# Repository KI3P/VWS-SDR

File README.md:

# Vienna Wireless Society Software Defined Receiver (VWS-SDR)

This repository contains the files for a 2025 project by the [Vienna Wireless Society's](https://viennawireless.net/wp/) Makers Group. This project aims to build the RF front end of a software defined receiver covering the HF bands. The goals of the project are: 

1. Learn how to use KiCAD, and 
2. Learn surface mount assembly techniques. 

## Credit

The VWS-SDR design draws heavily from the RF board of the T41-EP Software Defined Transceiver (SDT) originally designed by Al Peter-AC8GY and Jack Purdum-W8TEE. The T41-EP is a self-contain SDT that does not require an external PC, laptop, or tablet to use. Al and Jack wrote a book, available on [Amazon](https://www.amazon.com/dp/B0D25FV48C), describing the theory and operation of the T41-EP.

Thanks to Rick W1DSP for writing the Quisk integration, Barry KV4FV for the gnuradio demodulation flowgraph, the many T41 contributors for the hardware and software derived from that project, and to Leon NT8B, Dean KK4DAS, Mark KM4GML, Vlad K4LRZ, and Ed KQ4RVX for their help designing, building, and testing the prototypes.

## Design overview 

The VWS-SDR has stages shown in the block diagram below.

1. A gain stage based on the [GALI-S66+](https://www.minicircuits.com/WebStore/dashboard.html?model=GALI-S66%2B) MMIC amplifier.
2. A [Tayloe Mixer](http://norcalqrp.org/files/Tayloe_mixer_x3a.pdf) that uses quadrature signals generated by a [Si5351](https://www.digikey.com/en/htmldatasheets/production/1316951/0/0/1/si535x-tmstk) clock generator and a [74CBTLV3253](https://www.ti.com/product/SN74CBTLV3253) 2-channel analog multiplexer to mix the RF signals to IF.
3. An anti-aliasing low-pass filter followed by a USB soundcard to digitize the IF signal.
4. Demodulation is performed in software using [quisk](http://james.ahlstrom.name/quisk/) or [gnuradio](https://www.gnuradio.org/).

To modify the PCB design, download this repository to your computer. Open the `KiCad\VWS-SDR-ref-design.kicad_pro` file using the [KiCad](https://www.kicad.org/) EDA software package. This repository includes a few custom symbols and footprints that should automatically be added to your library lists by KiCad.

## Code

### Pico

You two equivalent choices for the code that will run on the Pico. If you prefer C code written in the Arduino framework, use that. If you prefer micropython code, load that code instead. 

#### Arduino framework

The `code/pico_sketch` folder contains an Arduino sketch to program the Pico. The sketch listens for ASCII commands on the USB serial bus (baud 115200) that match this format:

`FR 123456`

where `123456` is the frequency in Hertz that the Si5351 should be tuned to.

Open the sketch in the Arduino IDE and configure Arduino to have the settings shown below under the Tools menu. For “Port” select whatever COM port appears when you plug the Pico into your computer with a USB cable.

Then compile and load the sketch onto the pico by clicking the Upload button (Sketch->Upload).

The Pico sketch configures the Si5351 to produce 10 MHz tones on start. You can confirm this by connected an oscilloscope to the CLK0 and CLK1 outputs where you should see something like the screen shot below.

You can manually change the frequency using the Serial Monitor window in the Arduino. The Pico communicates at a baud rate of 115200 and expects commands in the form: “FR 123456” where 123456 is the frequency in Hz.

For instance, to tune the center of the band to 7070 kHz, enter the following command:

You should get the reply “OK” and an invitation to enter a new frequency. The CLK0 and CLK1 outputs should now show an output at 7070 kHz.

#### Micropython framework

The `code/pico_micropython` folder contains micropython code for the Pico written by Rick W1DSP. It works similarly to the Arduino sketch, the only difference is commands are terminated by a newline (`\n`) in the Python code, versus carriage return (`\r`) in the sketch. If the preferred tuner is the sketch, just edit this line in `code/VWS-Quisk/vwsquiskpkg/quisk_hardware.py`:

```python
   self.serial.write(b'FR %d\r'%(vfo+correction))
```

And change to `\r` to `\n`.  The original thinking in using Python for the VWS was to facilitate the extensive driver libraries Adafruit provides for their peripherals, as well as the ease of use and velocity of development Python brings to low speed control applications.

To install the Python tuner, the Pico must first be loaded with CircuitPython as described [here](https://learn.adafruit.com/getting-started-with-raspberry-pi-pico-circuitpython/circuitpython). Once CircuitPython is installed and booted, you will see a virtual disk drive for the board appear.  On my machine it is `/media/rick/CIRCUITPY`.

To run the tuner, copy `code/pico_micropython/{code.py,vws_tuner.py}`
to the virtual disk drive, and power cycle the board.  To verify operation, connnect to the serial port associated with the board (here, it is `/dev/ttyACM0`, 115200 bps), and type a carriage return.  You should see a `tune>` prompt, and entering a command like `FR 7074000` will cause the 5351 to tune to 7.074 Mhz. As required by the VWS SDR designs, clk0/clk1 are in quadrature. The Python script works similarly to various 5351 libraries to generate quadrature clocks: PLLA is a integer multiple of the desired frequency (factor of 4).

### Computer

Demodulation of the audio can be done in gnuradio or Quisk.

#### Gnuradio

Credit to Barry KV4FV for his contributions to the gnuradio code.

The `code/gnuradio_KI3P` contains a [gnuradio](https://wiki.gnuradio.org/index.php/InstallingGR) flowgraph to display the received signal and perform audio demodulation. It also allows you to adjust the gain and phase balance between the L and R channels to improve sideband separation if needed.

#### Quisk

Credit to Rick W1DSP for the Quisk code and instructions. Quisk links:

* [Quisk documentation](https://james.ahlstrom.name/quisk/docs.html)
* [Quisk github](https://github.com/jimahlstrom/quisk)
* [Install Quisk](https://james.ahlstrom.name/quisk/docs.html#Installation)

##### Install VWS-Quisk package

Once quisk is installed, copy the `code/VWS-Quisk/vwsquiskpkg` directory into the quisk distribution directory. On my computer this is:

* `/usr/lib/python3/dist-packages/quisk`

Note: This is the way new radios are introduced to the quisk radio configuration manager: for a new radio named `xyzzy`, you create a directory named `xyzzypkg` in the quisk directory, and write a `quisk_hardware.py` module.  Python class inheritance will define most of the necessary routines, but functionally you'll want open/close/tune method as shown in the `vwsquiskpkg` version.

##### Configure Quisk

Launch quisk.

To add the VWS SDR as a radio, click the Config Button, then select the Radios tab. In the Radios config panel, select the "Add a new radio with the general type", and select the VWS SDR item, name the radio "VWS"

You should see a new Radio appear just below the title bar named "VWS".  Click that item, and then select the Hardware tab.  Enter the serial port name (in my case it was `/dev/ttyACM0`). Click the Sound tab, and choose appropriate settings for "Radio Sound Output" and "Microphone Input" that correspond to your soundcard.  In Digital Rx0 line, select `pulse: Use name QuiskDigitalOutput.monitor`.  Of course, you'll need to have loaded the pulse audio system.  Note that I have not tested any of this on Mac or Windows, and wouldn't expect it to work out of the box on either system type.

Back on the Config->Radios screen, select VWS in the "When Quisk starts, use the radio" line. In the Config tab, quisk provides the ability to adjust IQ balance via "Adjust receive amplitude and phase".  I manually adjusted this using a signal generator tuned to the vicinity of 14.074 mhz, and then saved the result.

##### Configure WSJT-X if desired

To use the WSJT-X integration, use the package manager to install wsjtx, or build from source. 

I've been starting wsjtx manually within quisk: Click Config, select the Config tab, then look for the Start WSJT-X item.  The drop down menu has an option Main Rx0 Now item - select that and quisk will start the wsjtx application.  Once you've fully debugged the quisk:wsjtx integration,
setting "Start WSJT-X" to "Main Rx0 on startup" on the Config menus, Config tab will automatically start up wstjx when quisk starts.

The included screen captures show some of the details of getting quisk to interoperate with wsjtx.  Note that quisk won't stream audio on `QuiskDigitalOutput.monitor` unless you're in a digital mode (see DGT-U).

Quisk can be controlled by hamlib.  In the Config screens, select the VWS radio, then Remote tab.  On the Remote config screen, set the port to 4532.  You'll have to restart quisk for the setting to take effect.  After this is done, you can use `rigctl -m 2` to test: for example, the command `F 14074000` will tune quisk to the FT8 band on 20M.  Once the hamlib integration has been confirmed as working, you'll be able to control quisk via the wsjtx application, i.e. switching bands, frequencies in that app, and quisk following along as a normal radio would.

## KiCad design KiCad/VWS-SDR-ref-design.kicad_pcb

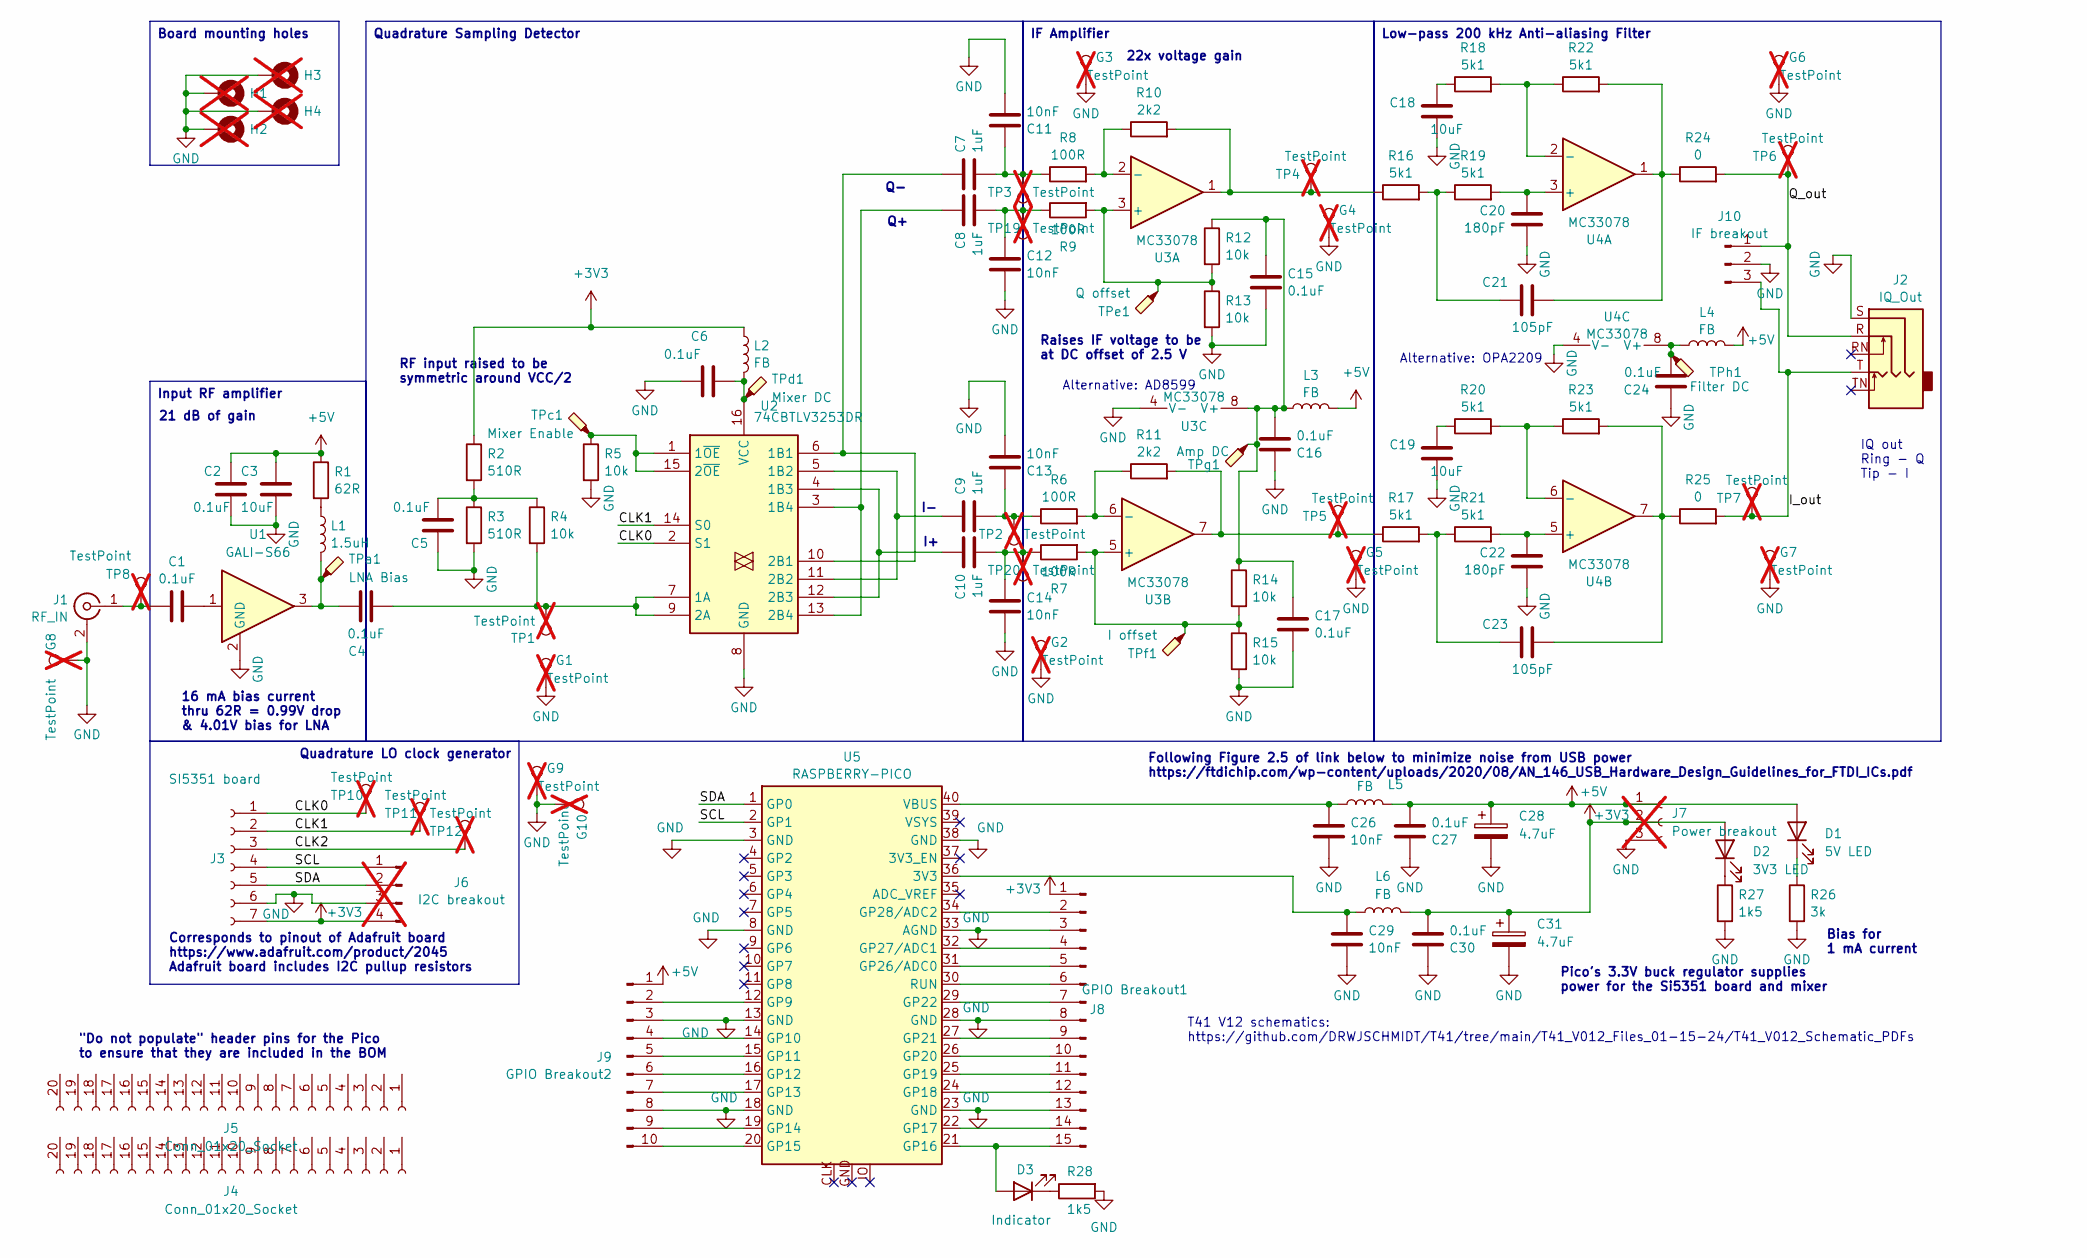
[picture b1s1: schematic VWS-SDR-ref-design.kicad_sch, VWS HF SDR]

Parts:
C1, C2, C4, C5, C6, C15, C16, C17, C24, C27, C30: 0.1uF; C_1206_3216Metric_Pad1.33x1.80mm_HandSolder; Mouser Part Number C1206C104K5RACTU
C3, C18, C19: 10uF; C_1206_3216Metric_Pad1.33x1.80mm_HandSolder; Mouser Part Number 80-C1206C106K4P
C7, C8, C9, C10: 1uF; C_1206_3216Metric_Pad1.33x1.80mm_HandSolder; Mouser Part Number 187-CL31B105KBHNNNE
C11, C12, C13, C14, C26, C29: 10nF; C_1206_3216Metric_Pad1.33x1.80mm_HandSolder; Mouser Part Number 80-C1206C103K5R7210
C20, C22: 180pF; C_1206_3216Metric_Pad1.33x1.80mm_HandSolder; Mouser Part Number 791-1206B181K160CT
C21, C23: 105pF; C_1206_3216Metric_Pad1.33x1.80mm_HandSolder; Mouser Part Number 581-12065C101KAT2A
C28, C31: 4.7uF; CP_Radial_D5.0mm_P2.00mm; Mouser Part Number 80-ESK475M016AC3AA
D1: 5V LED; LED_1206_3216Metric_Pad1.42x1.75mm_HandSolder; MPN APTD3216LCGCK
D2: 3V3 LED; LED_1206_3216Metric_Pad1.42x1.75mm_HandSolder; MPN APTD3216LSYCK
D3: Indicator; LED_1206_3216Metric_Pad1.42x1.75mm_HandSolder; MPN APTD3216LSYCK
G1, G2, G3, G4, G5, G6, G7, G8, G9, G10: TestPoint; PinHeader_1x01_P2.54mm_Vertical; not fitted
H1, H2, H3, H4: MountingHole_4.3mm_M4_DIN965_Pad; not fitted
J1: RF_IN; SMA_Vertical_and_Edgemount; Mouser Part Number 712-CONSMA001-G
J2: IQ_Out; Jack_3.5mm_STX-3081_Horizontal; Mouser Part Number 490-SJ1-3515N
J3: SI5351 board; Adafruit_Si5351
J4, J5: Conn_01x20_Socket
J6: I2C breakout; PinHeader_1x04_P2.54mm_Vertical; not fitted
J7: Power breakout; PinHeader_1x03_P2.54mm_Vertical; not fitted
J8: GPIO Breakout1; PinSocket_1x15_P2.54mm_Vertical
J9: GPIO Breakout2; PinSocket_1x10_P2.54mm_Vertical
J10: IF breakout; PinSocket_1x03_P2.54mm_Vertical
L1: 1.5uH; R_1206_3216Metric_Pad1.30x1.75mm_HandSolder; Mouser Part Number 81-LQM31PN1R5M00L
L2, L3, L4, L5, L6: FB; R_1206_3216Metric_Pad1.30x1.75mm_HandSolder; Mouser Part Number 875-HZ1206E601R-10
R1: 62R; R_1206_3216Metric_Pad1.30x1.75mm_HandSolder; Mouser Part Number 652-CR1206FX-62R0ELF
R2, R3: 510R; R_1206_3216Metric_Pad1.30x1.75mm_HandSolder; Mouser Part Number 652-CR1206FX-5100ELF
R4, R5, R12, R13, R14, R15: 10k; R_1206_3216Metric_Pad1.30x1.75mm_HandSolder; Mouser Part Number 652-CR1206FX-1002ELF
R6, R7, R8, R9: 100R; R_1206_3216Metric_Pad1.30x1.75mm_HandSolder; Mouser Part Number 652-CR1206FX-1000ELF
R10, R11: 2k2; R_1206_3216Metric_Pad1.30x1.75mm_HandSolder; Mouser Part Number 652-CR1206FX-2201ELF
R16, R17, R18, R19, R20, R21, R22, R23: 5k1; R_1206_3216Metric_Pad1.30x1.75mm_HandSolder; Mouser Part Number 652-CR1206JW-512ELF
R24, R25: 0; R_1206_3216Metric_Pad1.30x1.75mm_HandSolder; Mouser Part Number 71-CRCW12060000Z0EAC
R26: 3k; R_1206_3216Metric_Pad1.30x1.75mm_HandSolder; MPN CR1206-FX-3001ELF
R27, R28: 1k5; R_1206_3216Metric_Pad1.30x1.75mm_HandSolder; MPN CR1206-FX-1501ELF
TP1, TP2, TP3, TP4, TP5, TP6, TP7, TP8, TP10, TP11, TP12, TP19, TP20: TestPoint; PinHeader_1x01_P2.54mm_Vertical; not fitted
TPa1: LNA Bias; TestPoint_Pad_D1.5mm
TPc1: Mixer Enable; TestPoint_Pad_D1.5mm
TPd1: Mixer DC; TestPoint_Pad_D1.5mm
TPe1: Q offset; TestPoint_Pad_D1.5mm
TPf1: I offset; TestPoint_Pad_D1.5mm
TPg1: Amp DC; TestPoint_Pad_D1.5mm
TPh1: Filter DC; TestPoint_Pad_D1.5mm
U1: GALI-S66; SOT-89-3; Mouser Part Number 139-GALI-S66
U2: 74CBTLV3253DR; SOIC-16_3.9x9.9mm_P1.27mm; Mouser Part Number 595-SN74CBTLV3253DR
U3, U4: MC33078; SOIC-8_3.9x4.9mm_P1.27mm; Mouser Part Number 595-MC33078DR
U5: RASPBERRY-PICO; Raspberry_pico_pin_or_castellation_footprint; Mouser Part Number 358-SC0915

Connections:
+3V3: C30.1, C31.1, D2.2 (A), J3.7, J6.4, J7.2, J8.1, L2.1, L6.2, R2.1
+5V: C2.2, C3.2, C27.1, C28.1, D1.2 (A), J7.1, J9.1, L3.2, L4.2, L5.2, R1.1
/CLK0: J3.1, TP10.1, U2.2 (S1)
/CLK1: J3.2, TP11.1, U2.14 (S0)
/CLK2: J3.3, TP12.1
/I_out: J2.T, J10.3, R25.2, TP7.1
/Q_out: J2.R, J10.1, R24.2, TP6.1
/SCL: J3.4, J6.1, U5.2 (GP1)
/SDA: J3.5, J6.2, U5.1 (GP0)
GND: C2.1, C3.1, C5.1, C6.1, C11.1, C12.1, C13.1, C14.1, C15.1, C16.2, C17.1, C18.1, C19.1, C20.1, C22.1, C24.2, C26.1, C27.2, C28.2, C29.1, C30.2, C31.2, G1.1, G2.1, G3.1, G4.1, G5.1, G6.1, G7.1, G8.1, G9.1, G10.1, H1.1, H2.1, H3.1, H4.1, J1.2 (Ext), J2.S, J3.6, J6.3, J7.3, J8.3, J8.8, J8.13, J9.3, J9.8, J10.2, R3.2, R5.2, R13.2, R15.2, R26.2, R27.2, R28.2, U1.2 (GND), U2.8 (GND), U3.4 (V-), U4.4 (V-), U5.3 (GND), U5.8 (GND), U5.13 (GND), U5.18 (GND), U5.23 (GND), U5.28 (GND), U5.33 (AGND), U5.38 (GND)
unnamed: C1.2, U1.1
unnamed 11: C4.1, L1.2, TPa1.1, U1.3; also elsewhere on the board
unnamed: C5.2, R2.2, R3.1, R4.1
unnamed: C10.1, C14.2, R7.1, TP20.1
unnamed: C7.1, C11.2, R8.1, TP3.1
unnamed: C8.1, C12.2, R9.1, TP19.1
unnamed: C9.1, C13.2, R6.1, TP2.1
unnamed: C18.2, R18.1
unnamed: C19.2, R20.1
unnamed: C21.1, R22.2, R24.1, U4.1
unnamed: C21.2, R16.2, R19.1
unnamed: C23.1, R23.2, R25.1, U4.7
unnamed: C23.2, R17.2, R21.1
unnamed: D1.1 (K), R26.1
unnamed: D2.1 (K), R27.1
unnamed: D3.2 (A), J8.15, U5.21 (GP16)
unnamed: D3.1 (K), R28.1
unnamed: C1.1, J1.1 (In), TP8.1
unnamed: J8.2, U5.34 (GP28/ADC2)
unnamed: J8.4, U5.32 (GP27/ADC1)
unnamed: J8.5, U5.31 (GP26/ADC0)
unnamed: J8.6, U5.30 (RUN)
unnamed: J8.7, U5.29 (GP22)
unnamed: J8.9, U5.27 (GP21)
unnamed: J8.10, U5.26 (GP20)
unnamed: J8.11, U5.25 (GP19)
unnamed: J8.12, U5.24 (GP18)
unnamed: J8.14, U5.22 (GP17)
unnamed: J9.2, U5.12 (GP9)
unnamed: J9.4, U5.14 (GP10)
unnamed: J9.5, U5.15 (GP11)
unnamed: J9.6, U5.16 (GP12)
unnamed: J9.7, U5.17 (GP13)
unnamed: J9.9, U5.19 (GP14)
unnamed: J9.10, U5.20 (GP15)
unnamed: L1.1, R1.2
unnamed: R10.2, R16.1, TP4.1, U3.1
unnamed: R11.2, R17.1, TP5.1, U3.7
unnamed 48: C4.2, R4.2, TP1.1, U2.7 (1A), U2.9 (2A); also elsewhere on the board
unnamed: C7.2, U2.6 (1B1), U2.10 (2B1)
unnamed: C9.2, U2.5 (1B2), U2.11 (2B2)
unnamed: C10.2, U2.4 (1B3), U2.12 (2B3)
unnamed: C8.2, U2.3 (1B4), U2.13 (2B4)
unnamed 53: R5.1, TPc1.1, U2.1 (1~OE), U2.15 (2~OE); also elsewhere on the board
unnamed 54: C6.2, L2.2, TPd1.1, U2.16 (VCC); also elsewhere on the board
unnamed 55: R9.2, R12.2, R13.1, TPe1.1, U3.3 (+); also elsewhere on the board
unnamed: R8.2, R10.1, U3.2 (-)
unnamed 57: R7.2, R14.2, R15.1, TPf1.1, U3.5 (+); also elsewhere on the board
unnamed: R6.2, R11.1, U3.6 (-)
unnamed 59: C15.2, C16.1, C17.2, L3.1, R12.1, R14.1, TPg1.1, U3.8 (V+); also elsewhere on the board
unnamed: C20.2, R19.2, U4.3 (+)
unnamed: R18.2, R22.1, U4.2 (-)
unnamed: C22.2, R21.2, U4.5 (+)
unnamed: R20.2, R23.1, U4.6 (-)
unnamed 64: C24.1, L4.1, TPh1.1, U4.8 (V+); also elsewhere on the board
unnamed: C29.2, L6.1, U5.36 (3V3)
unnamed: C26.2, L5.1, U5.40 (VBUS)

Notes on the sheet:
Raises IF voltage to be at DC offset of 2.5 V
T41 V12 schematics: https://github.com/DRWJSCHMIDT/T41/tree/main/T41_V012_Files_01-15-24/T41_V012_Schematic_PDFs
Bias for 1 mA current
Following Figure 2.5 of link below to minimize noise from USB power https://ftdichip.com/wp-content/uploads/2020/08/AN_146_USB_Hardware_Design_Guidelines_for_FTDI_ICs.pdf
Pico's 3.3V buck regulator supplies power for the Si5351 board and mixer
Alternative: OPA2209
21 dB of gain
Alternative: AD8599
"Do not populate" header pins for the Pico to ensure that they are included in the BOM
16 mA bias current thru 62R = 0.99V drop & 4.01V bias for LNA
IQ out Ring - Q Tip - I
22x voltage gain
RF input raised to be symmetric around VCC/2
Corresponds to pinout of Adafruit board https://www.adafruit.com/product/2045 Adafruit board includes I2C pullup resistors
Quadrature LO clock generator
IF Amplifier
Low-pass 200 kHz Anti-aliasing Filter
Quadrature Sampling Detector
Input RF amplifier
Board mounting holes

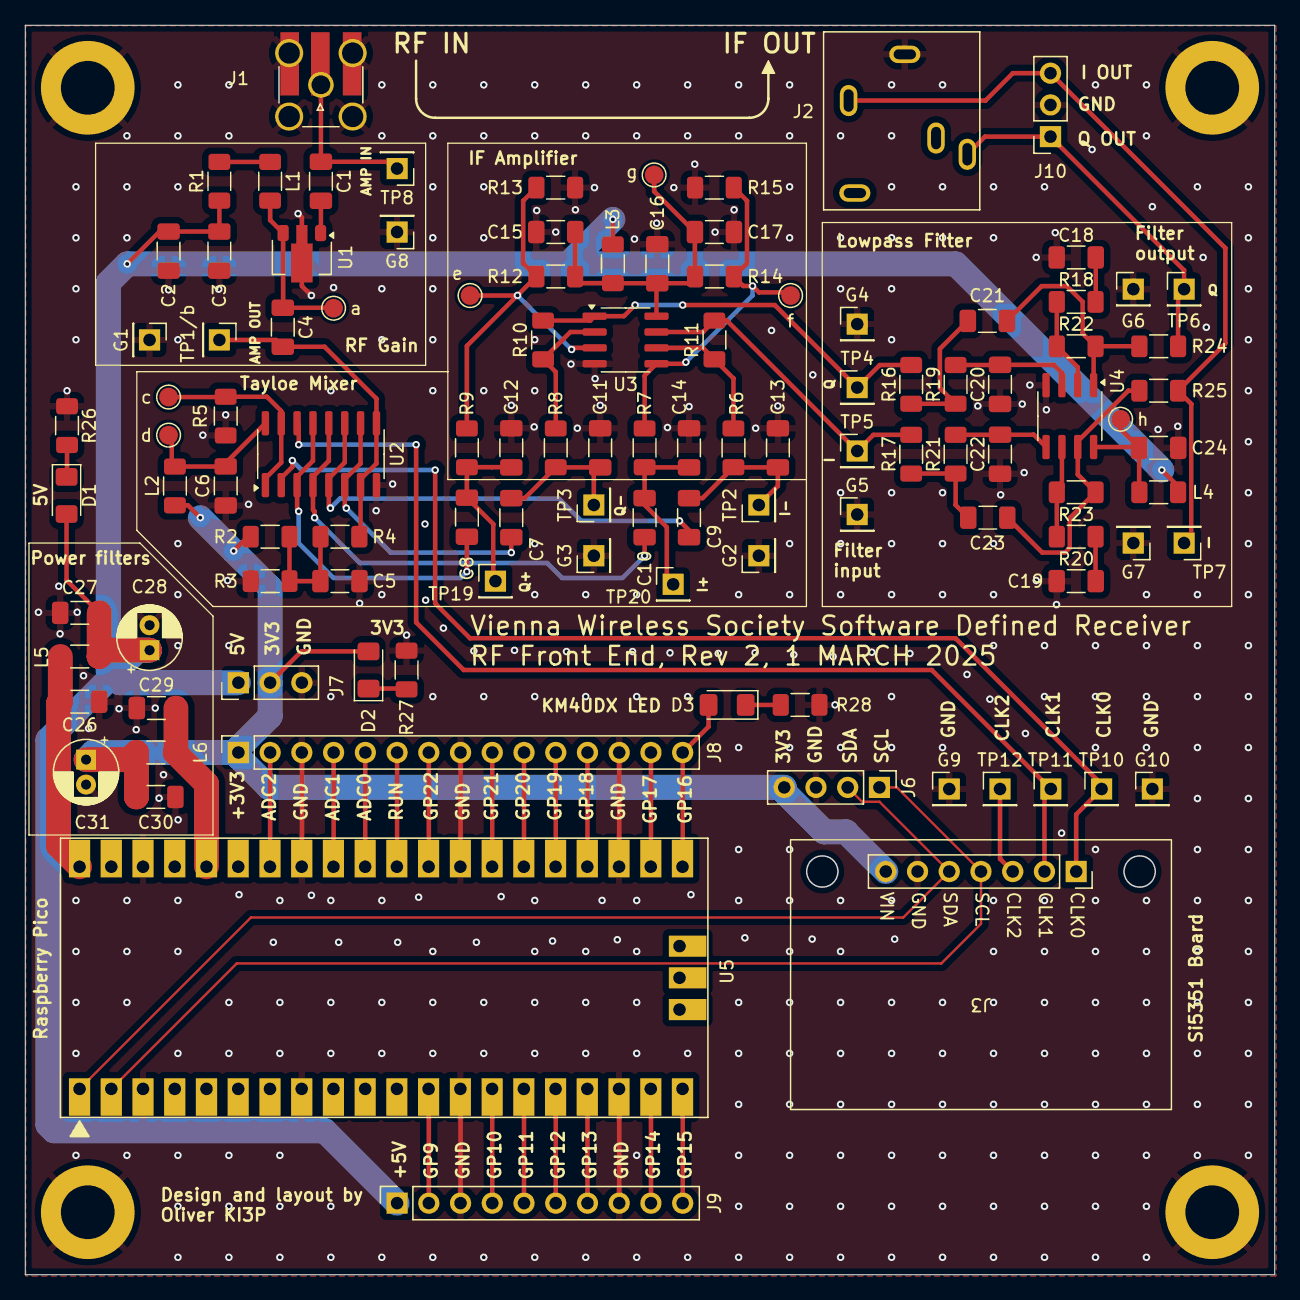
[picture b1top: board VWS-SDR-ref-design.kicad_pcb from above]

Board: 4 copper layers, 99.9 x 99.9 mm, 114 parts (0 on the bottom side), 67 nets.

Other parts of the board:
TP1/b: TestPoint; PinHeader_1x01_P2.54mm_Vertical
a: LNA Bias; TestPoint_Pad_D1.5mm
c: Mixer Enable; TestPoint_Pad_D1.5mm
d: Mixer DC; TestPoint_Pad_D1.5mm
e: Q offset; TestPoint_Pad_D1.5mm
f: I offset; TestPoint_Pad_D1.5mm
g: Amp DC; TestPoint_Pad_D1.5mm
h: Filter DC; TestPoint_Pad_D1.5mm

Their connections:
unnamed 11: a.1; also elsewhere on the board
unnamed 48: TP1/b.1; also elsewhere on the board
unnamed 53: c.1; also elsewhere on the board
unnamed 54: d.1; also elsewhere on the board
unnamed 55: e.1; also elsewhere on the board
unnamed 57: f.1; also elsewhere on the board
unnamed 59: g.1; also elsewhere on the board
unnamed 64: h.1; also elsewhere on the board

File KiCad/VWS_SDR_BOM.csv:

"Reference","Value","Footprint","Qty","DNP","Tayda","Adafruit PN","MPN"
"C1,C2,C4,C5,C6,C15,C16,C17,C24,C27,C30","0.1uF","Capacitor_SMD:C_1206_3216Metric_Pad1.33x1.80mm_HandSolder","11","","","","C1206C104K5RACTU"
"C3,C18,C19","10uF","Capacitor_SMD:C_1206_3216Metric_Pad1.33x1.80mm_HandSolder","3","","","","C1206C106K4PACTU"
"C7,C8,C9,C10","1uF","Capacitor_SMD:C_1206_3216Metric_Pad1.33x1.80mm_HandSolder","4","","","","KGM31HR71C105KU"
"C11,C12,C13,C14,C26,C29","10nF","Capacitor_SMD:C_1206_3216Metric_Pad1.33x1.80mm_HandSolder","6","","","","C1206C103K5RAC7210"
"C20,C22","180pF","Capacitor_SMD:C_1206_3216Metric_Pad1.33x1.80mm_HandSolder","2","","","","KGM31BCG2A181FT"
"C21,C23","105pF","Capacitor_SMD:C_1206_3216Metric_Pad1.33x1.80mm_HandSolder","2","","","","C3216C0G2J101G060AA"
"C28,C31","4.7uF","Capacitor_THT:CP_Radial_D5.0mm_P2.00mm","2","","","","ESK475M016AC3AA"
"D1","5V LED","LED_SMD:LED_1206_3216Metric_Pad1.42x1.75mm_HandSolder","1","","","","APTD3216LCGCK"
"D2","3V3 LED","LED_SMD:LED_1206_3216Metric_Pad1.42x1.75mm_HandSolder","1","","","","APTD3216LSYCK"
"D3","Indicator","LED_SMD:LED_1206_3216Metric_Pad1.42x1.75mm_HandSolder","1","","","","APTD3216LSYCK"
"G1,G2,G3,G4,G5,G6,G7,G8,G9,G10,TP1,TP2,TP3,TP4,TP5,TP6,TP7,TP8,TP10,TP11,TP12,TP19,TP20","TestPoint","Connector_PinHeader_2.54mm:PinHeader_1x01_P2.54mm_Vertical","23","DNP","","",""
"J1","RF_IN","VWS-SDR:SMA_Vertical_and_Edgemount","1","","","","CONSMA001-G"
"J2","IQ_Out","VWS-SDR:Jack_3.5mm_STX-3081_Horizontal","1","","","","SJ1-3515N"
"J3","SI5351 board","VWS-SDR:Adafruit_Si5351","1","","","2045",""
"J4,J5","Conn_01x20_Socket","","2","","A-1310","",""
"J6","I2C breakout","Connector_PinHeader_2.54mm:PinHeader_1x04_P2.54mm_Vertical","1","DNP","","",""
"J7","Power breakout","Connector_PinHeader_2.54mm:PinHeader_1x03_P2.54mm_Vertical","1","DNP","","",""
"J8","GPIO Breakout1","Connector_PinSocket_2.54mm:PinSocket_1x15_P2.54mm_Vertical","1","","A-1669","",""
"J9","GPIO Breakout2","Connector_PinSocket_2.54mm:PinSocket_1x10_P2.54mm_Vertical","1","","A-1306","",""
"J10","IF breakout","Connector_PinSocket_2.54mm:PinSocket_1x03_P2.54mm_Vertical","1","","A-1069","",""
"L1","1.5uH","Resistor_SMD:R_1206_3216Metric_Pad1.30x1.75mm_HandSolder","1","","","","LQM31PN1R5M00L"
"L2,L3,L4,L5,L6","FB","Resistor_SMD:R_1206_3216Metric_Pad1.30x1.75mm_HandSolder","5","","","","HZ1206E601R-10"
"R1","62R","Resistor_SMD:R_1206_3216Metric_Pad1.30x1.75mm_HandSolder","1","","","","CR1206-FX-62R0ELF"
"R2,R3","510R","Resistor_SMD:R_1206_3216Metric_Pad1.30x1.75mm_HandSolder","2","","","","CR1206-FX-5100ELF"
"R4,R5,R12,R13,R14,R15","10k","Resistor_SMD:R_1206_3216Metric_Pad1.30x1.75mm_HandSolder","6","","","","CR1206-FX-1002ELF"
"R6,R7,R8,R9","100R","Resistor_SMD:R_1206_3216Metric_Pad1.30x1.75mm_HandSolder","4","","","","CR1206-FX-1000ELF"
"R10,R11","2k2","Resistor_SMD:R_1206_3216Metric_Pad1.30x1.75mm_HandSolder","2","","","","CR1206-FX-2201ELF"
"R16,R17,R18,R19,R20,R21,R22,R23","5k1","Resistor_SMD:R_1206_3216Metric_Pad1.30x1.75mm_HandSolder","8","","","","CR1206-JW-512ELF"
"R24,R25","0","Resistor_SMD:R_1206_3216Metric_Pad1.30x1.75mm_HandSolder","2","","","","CRCW12060000Z0EAC"
"R26","3k","Resistor_SMD:R_1206_3216Metric_Pad1.30x1.75mm_HandSolder","1","","","","CR1206-FX-3001ELF"
"R27,R28","1k5","Resistor_SMD:R_1206_3216Metric_Pad1.30x1.75mm_HandSolder","2","","","","CR1206-FX-1501ELF"
"TPa1","LNA Bias","TestPoint:TestPoint_Pad_D1.5mm","1","","","",""
"TPc1","Mixer Enable","TestPoint:TestPoint_Pad_D1.5mm","1","","","",""
"TPd1","Mixer DC","TestPoint:TestPoint_Pad_D1.5mm","1","","","",""
"TPe1","Q offset","TestPoint:TestPoint_Pad_D1.5mm","1","","","",""
"TPf1","I offset","TestPoint:TestPoint_Pad_D1.5mm","1","","","",""
"TPg1","Amp DC","TestPoint:TestPoint_Pad_D1.5mm","1","","","",""
"TPh1","Filter DC","TestPoint:TestPoint_Pad_D1.5mm","1","","","",""
"U1","GALI-S66","Package_TO_SOT_SMD:SOT-89-3","1","","","","GALI-S66+"
"U2","74CBTLV3253DR","Package_SO:SOIC-16_3.9x9.9mm_P1.27mm","1","","","","SN74CBTLV3253DR"
"U3,U4","MC33078","Package_SO:SOIC-8_3.9x4.9mm_P1.27mm","2","","","","MC33078DR"
"U5","RASPBERRY-PICO","VWS-SDR:Raspberry_pico_pin_or_castellation_footprint","1","","","","SC0915"

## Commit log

2025-01-09 Added the KiCad files containing the reference schematic
2025-01-25 Placement complete, next step routing
2025-01-25 Layout complete
2025-02-16 Added part selection
2025-02-17 Basic software for pico and gnuradio interface to control it
2025-02-22 Added BOM
2025-02-22 Fixed the frequency tuning in the gnuradio sketch
2025-02-23 Added some pictures
2025-02-23 Minor update to block diagram
2025-02-23 Added Quisk integration
2025-02-23 remove wrong sound card -- it only supported mono input, not stereo
2025-03-22 Update for Rev 2 of the board
2025-03-22 Turn an LED on during setup for testing purposes
2025-04-05 Added instructions
2025-04-06 Added Windows sound instructions
2025-05-11 Updated the Quisk instructions
2025-05-31 Improvements to the gnuradio flowgraph

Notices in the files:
KiCad/VWS-SDR-ref-design.kicad_pcb:
GPLV3
